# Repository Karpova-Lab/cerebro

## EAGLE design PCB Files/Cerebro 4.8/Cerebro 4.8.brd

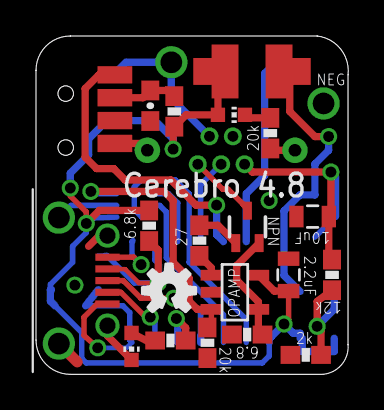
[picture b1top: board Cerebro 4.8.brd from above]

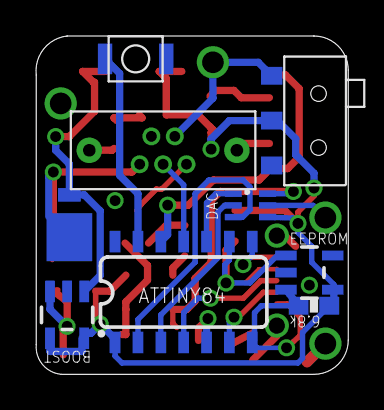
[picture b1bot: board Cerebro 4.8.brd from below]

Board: 2 copper layers, 17.3 x 18.8 mm, 31 parts (8 on the bottom side), 26 nets.

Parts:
C1: .1uF; 0603-CAP
C3: 2.2uF; 0805
C4: 10uF; 0805
D1: MBRM140T3G; POWERMITE
GROUND: BATT_TERMINAL
IC1: OPA237N; SOT23-5
INDICATOR_LED, INDICATOR_LED1: LED; CHIP-LED0603
L1: 10uH; 1812
LASER_OUTPUT: USB_MICROB_PLUG-PTH2; MICRO-B-TH
MIC2288: BOOST; SOT23-5
R1: 27; 0603-RES
R2: 6.8; 0603-RES
R3: 2k; 0603-RES
R4: 12k; 0603-RES
R5, R8, R9: 20k; 0603-RES
R6, R7: 6.8k; 0603-RES
R10: 100; 0603-RES
S3: SWITCH-SPDT-SMD
SDF: TSOP6238TT; TSOP6
SERIAL_SOCKET: USB_SOCKET_MICRO_VERTREINFORCED; USB_HORZ_REINFORCED_MICRO
T1: FJX3904TF; SOT323
U$1: DAC_LTC2630; SC-70
U$2: ATTINY84; SO14
U$3: SWITCH-MOMENTARY-NO; SWITCH_MOMENTARY_XS
U$4: EEPROM24C64A; SOT23-5
U$6: OSHW-LOGO-S
U$8: BATT_TERMINAL

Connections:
8.68VDC: C4.1, D1.CATHODE, LASER_OUTPUT.5, R4.2
BATT: C3.1, IC1.5, INDICATOR_LED.A, L1.P$2, L1.P$4, MIC2288.4, MIC2288.5, R6.2, R7.2, R10.1, S3.2, U$1.VCC, U$2.1, U$4.4
GND: C1.2, C3.2, C4.2, GROUND.P$1, IC1.2, INDICATOR_LED1.C, LASER_OUTPUT.4, LASER_OUTPUT.P$1, LASER_OUTPUT.P$2, MIC2288.2, R2.2, R3.1, R5.2, R8.2, S3.3, SDF.P$1, SDF.P$2, SERIAL_SOCKET.G1, SERIAL_SOCKET.G2, SERIAL_SOCKET.P$1, SERIAL_SOCKET.P$2, U$1.GND, U$2.14, U$3.P$2, U$4.2
MISO/TX: SERIAL_SOCKET.P1, U$2.8
MOSI: R7.1, SERIAL_SOCKET.P5, U$2.7, U$4.3
unnamed: SDF.P$4, U$2.12
unnamed: U$1.CS/LD, U$2.10
unnamed: IC1.3, R8.1, U$1.VOUT
unnamed: LASER_OUTPUT.2, S3.1, U$8.P$1
unnamed: LASER_OUTPUT.3, U$2.11
unnamed: IC1.4, R2.1, T1.3
unnamed: U$2.13, U$3.P$1
unnamed: INDICATOR_LED.C, R5.1
unnamed: IC1.1, R1.2
unnamed: MIC2288.3, R3.2, R4.1
unnamed: R1.1, T1.2
unnamed: C1.1, R10.2, SDF.P$3
unnamed: R9.1, U$2.5
unnamed: U$1.SCK, U$2.3
unnamed: D1.ANODE, L1.P$1, L1.P$3, MIC2288.1
unnamed: U$1.SDI, U$2.2
unnamed: LASER_OUTPUT.1, T1.1
unnamed: INDICATOR_LED1.A, R9.2
RESET: SERIAL_SOCKET.P3, U$2.4
RX: SERIAL_SOCKET.P4, U$2.6
SCK: R6.1, SERIAL_SOCKET.P2, U$2.9, U$4.1

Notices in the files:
parts and their libraries:
SparkFun-DigitalIC: Licensing: Creative Commons ShareAlike 4.0 International - https://creativecommons.org/licenses/by-sa/4.0
